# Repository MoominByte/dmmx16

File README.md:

# BenchScan DMMX16

BenchScan DMMX16 is a digital multimeter switching card inspired by the functional architecture of the SIGLENT SC1016. It provides 16 measurement channels: 12 multipurpose channels and 4 fuse-protected current channels.

## Project status

- Schematic revision: **DRAFT-1**
- File format: **KiCad 10**
- Hierarchical schematic converted and saved
- ERC: **0 errors and 18 off-grid warnings** from the custom MOSFET symbols
- PCB: **220 × 110 mm**, four copper layers, with all 113 footprints placed on the top side
- Preliminary placement completed; routing and manufacturing files have not started

This project is not ready for manufacturing.

## Opening the project

Open `BenchScan_DMMX16.kicad_pro` with KiCad 10. The modern root schematic is `BenchScan_DMMX16.kicad_sch`.

The legacy `.sch` files are retained as conversion sources. The earlier architecture-only draft is preserved under `archive/architecture-notes-draft0/`.

## Architecture

### Control

- Main module: Seeed Studio XIAO ESP32-C6, U1
- D0 / GPIO0: serial data `SER`
- D1 / GPIO1: shift clock `SRCLK`
- D2 / GPIO2: register clock `RCLK`
- D3 / GPIO21: active-low output enable `/OE`
- D4 / GPIO22: direct K17 control
- U2 and U3: two SN74HC595 shift registers powered by the XIAO 3.3 V output
- U2 controls K1-K8 and U3 controls K9-K16

Each relay is driven by a 2N7002K MOSFET with a 100 ohm series gate resistor, a 47 kohm gate pull-down, and a 1N4148W flyback diode. K17 uses the same driver circuit but receives its control signal directly from the XIAO.

### Measurement channels

| Connector | Channels | Purpose |
| --- | --- | --- |
| J1 | CH1-CH4 | Voltage, resistance, frequency, capacitance, diode, continuity, and temperature |
| J2 | CH5-CH8 | Multipurpose measurement and associated SENSE channels |
| J3 | CH9-CH12 | Multipurpose measurement and associated SENSE channels |
| J4 | CH13-CH16 | Current measurement, provisional 500 mA maximum |

Each J1-J4 connector has eight positions at 5.00 mm pitch: one `HI` and one `LO` terminal for each of its four channels.

### Switching

- K1-K16 use normally open contacts.
- K1-K6 route directly to `INPUT_HI` and `COM`.
- K7-K12 are routed through K17.
- With K17 de-energized, K7-K12 are routed to `INPUT_HI` and `COM`.
- With K17 energized, K7-K12 are routed to `SENSE_HI` and `SENSE_LO`.
- The four-wire pairs are CH1+CH7, CH2+CH8, CH3+CH9, CH4+CH10, CH5+CH11, and CH6+CH12.
- K13-K16 route the current channels to `CURRENT_HI` and `CURRENT_LO`.

Firmware must prevent multiple channels from being connected to the same destination bus at the same time, except for one valid four-wire pair.

### Current-channel protection

F1-F4 are Littelfuse `0451.500MRL` fast-acting 500 mA, 125 V fuses. They must not be replaced by 0.1 ohm resistors without a new circuit and safety analysis.

### DMM interface

J5 and the six banana jacks expose:

- `INPUT_HI`
- `COM`
- `SENSE_HI`
- `SENSE_LO`
- `CURRENT_HI`
- `CURRENT_LO`

R50 is a default-fitted 0 ohm link between `CURRENT_LO` and `COM`, with accessible test points planned on both sides.

### Power

- The XIAO is powered through its USB-C connector.
- The barrel jack supplies only the `+5V_RELAY` rail through F6 and Q19.
- USB, logic, and relay grounds are common.
- The external 5 V supply is not connected directly to the XIAO VBUS pin, preventing backfeed into USB.

## Schematic structure

- `01_power_control.kicad_sch`: XIAO, shift registers, and power supply
- `02_relay_drivers.kicad_sch`: 17 relay-coil drivers
- `03_voltage_channels.kicad_sch`: CH1-CH12 and normal/sense selection
- `04_current_dmm_interface.kicad_sch`: CH13-CH16, fuses, and DMM interface

Supporting documents:

- `BOM_AUDIT.md`: bill-of-materials review
- `CONNECTOR_PINOUT.csv`: J1-J4 pin assignments
- `SWITCHING_TRUTH_TABLE.md`: switching truth table
- `PLACEMENT_CONSTRAINTS.md`: mechanical and placement constraints
- `SC1016_REFERENCE.md`: SC1016 reference specifications
- `erc-placement.json`: latest automated ERC report
- `drc-placement.json`: preliminary placement DRC report (routing intentionally incomplete)
- `LIBRARY_SOURCES.md`: footprint provenance and manufacturer references

## Required before routing

1. Align the custom MOSFET symbol pins to eliminate the 18 ERC off-grid warnings.
2. Verify the gate, source, and drain pin mapping of Q1-Q19 against the selected SOT-23 footprint.
3. Mechanically verify the four project-created footprints against physical samples or manufacturer drawings before ordering boards.
4. Confirm voltage limits, creepage and clearance requirements, trace-width rules, and internal plane strategy.
5. Review and refine the preliminary placement, especially edge access and measurement-signal return paths.
6. Complete a manual schematic and PCB review before routing and manufacturing-output generation.

## Warning

The SC1016 ratings are used only as a functional reference. They do not certify the electrical limits of this board. A complete safety and manufacturability review is required before ordering PCBs.

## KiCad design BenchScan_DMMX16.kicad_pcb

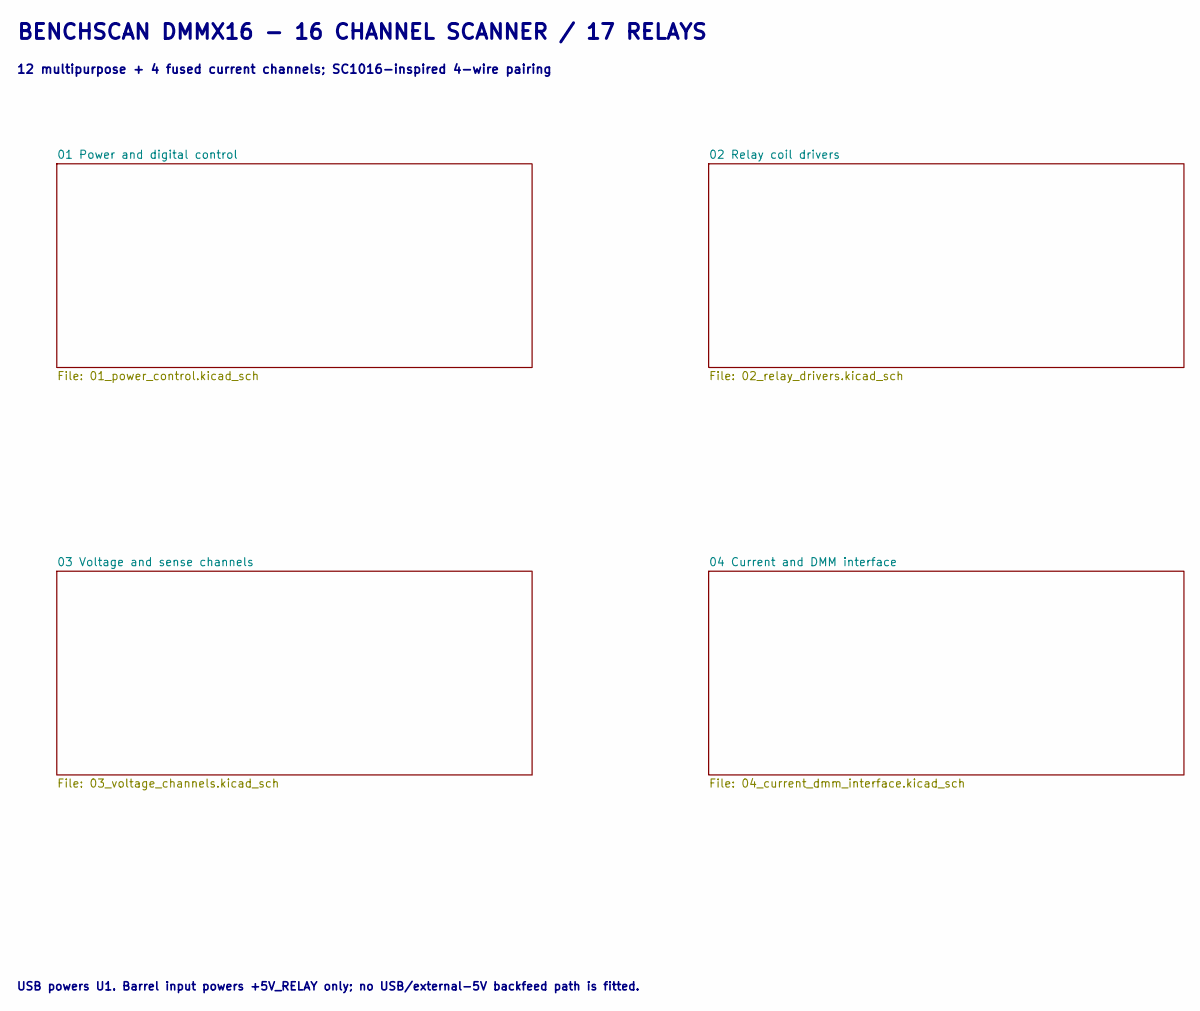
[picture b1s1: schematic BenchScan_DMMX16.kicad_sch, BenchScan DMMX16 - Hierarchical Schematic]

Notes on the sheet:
12 multipurpose + 4 fused current channels; SC1016-inspired 4-wire pairing
USB powers U1. Barrel input powers +5V_RELAY only; no USB/external-5V backfeed path is fitted.
BENCHSCAN DMMX16 - 16 CHANNEL SCANNER / 17 RELAYS

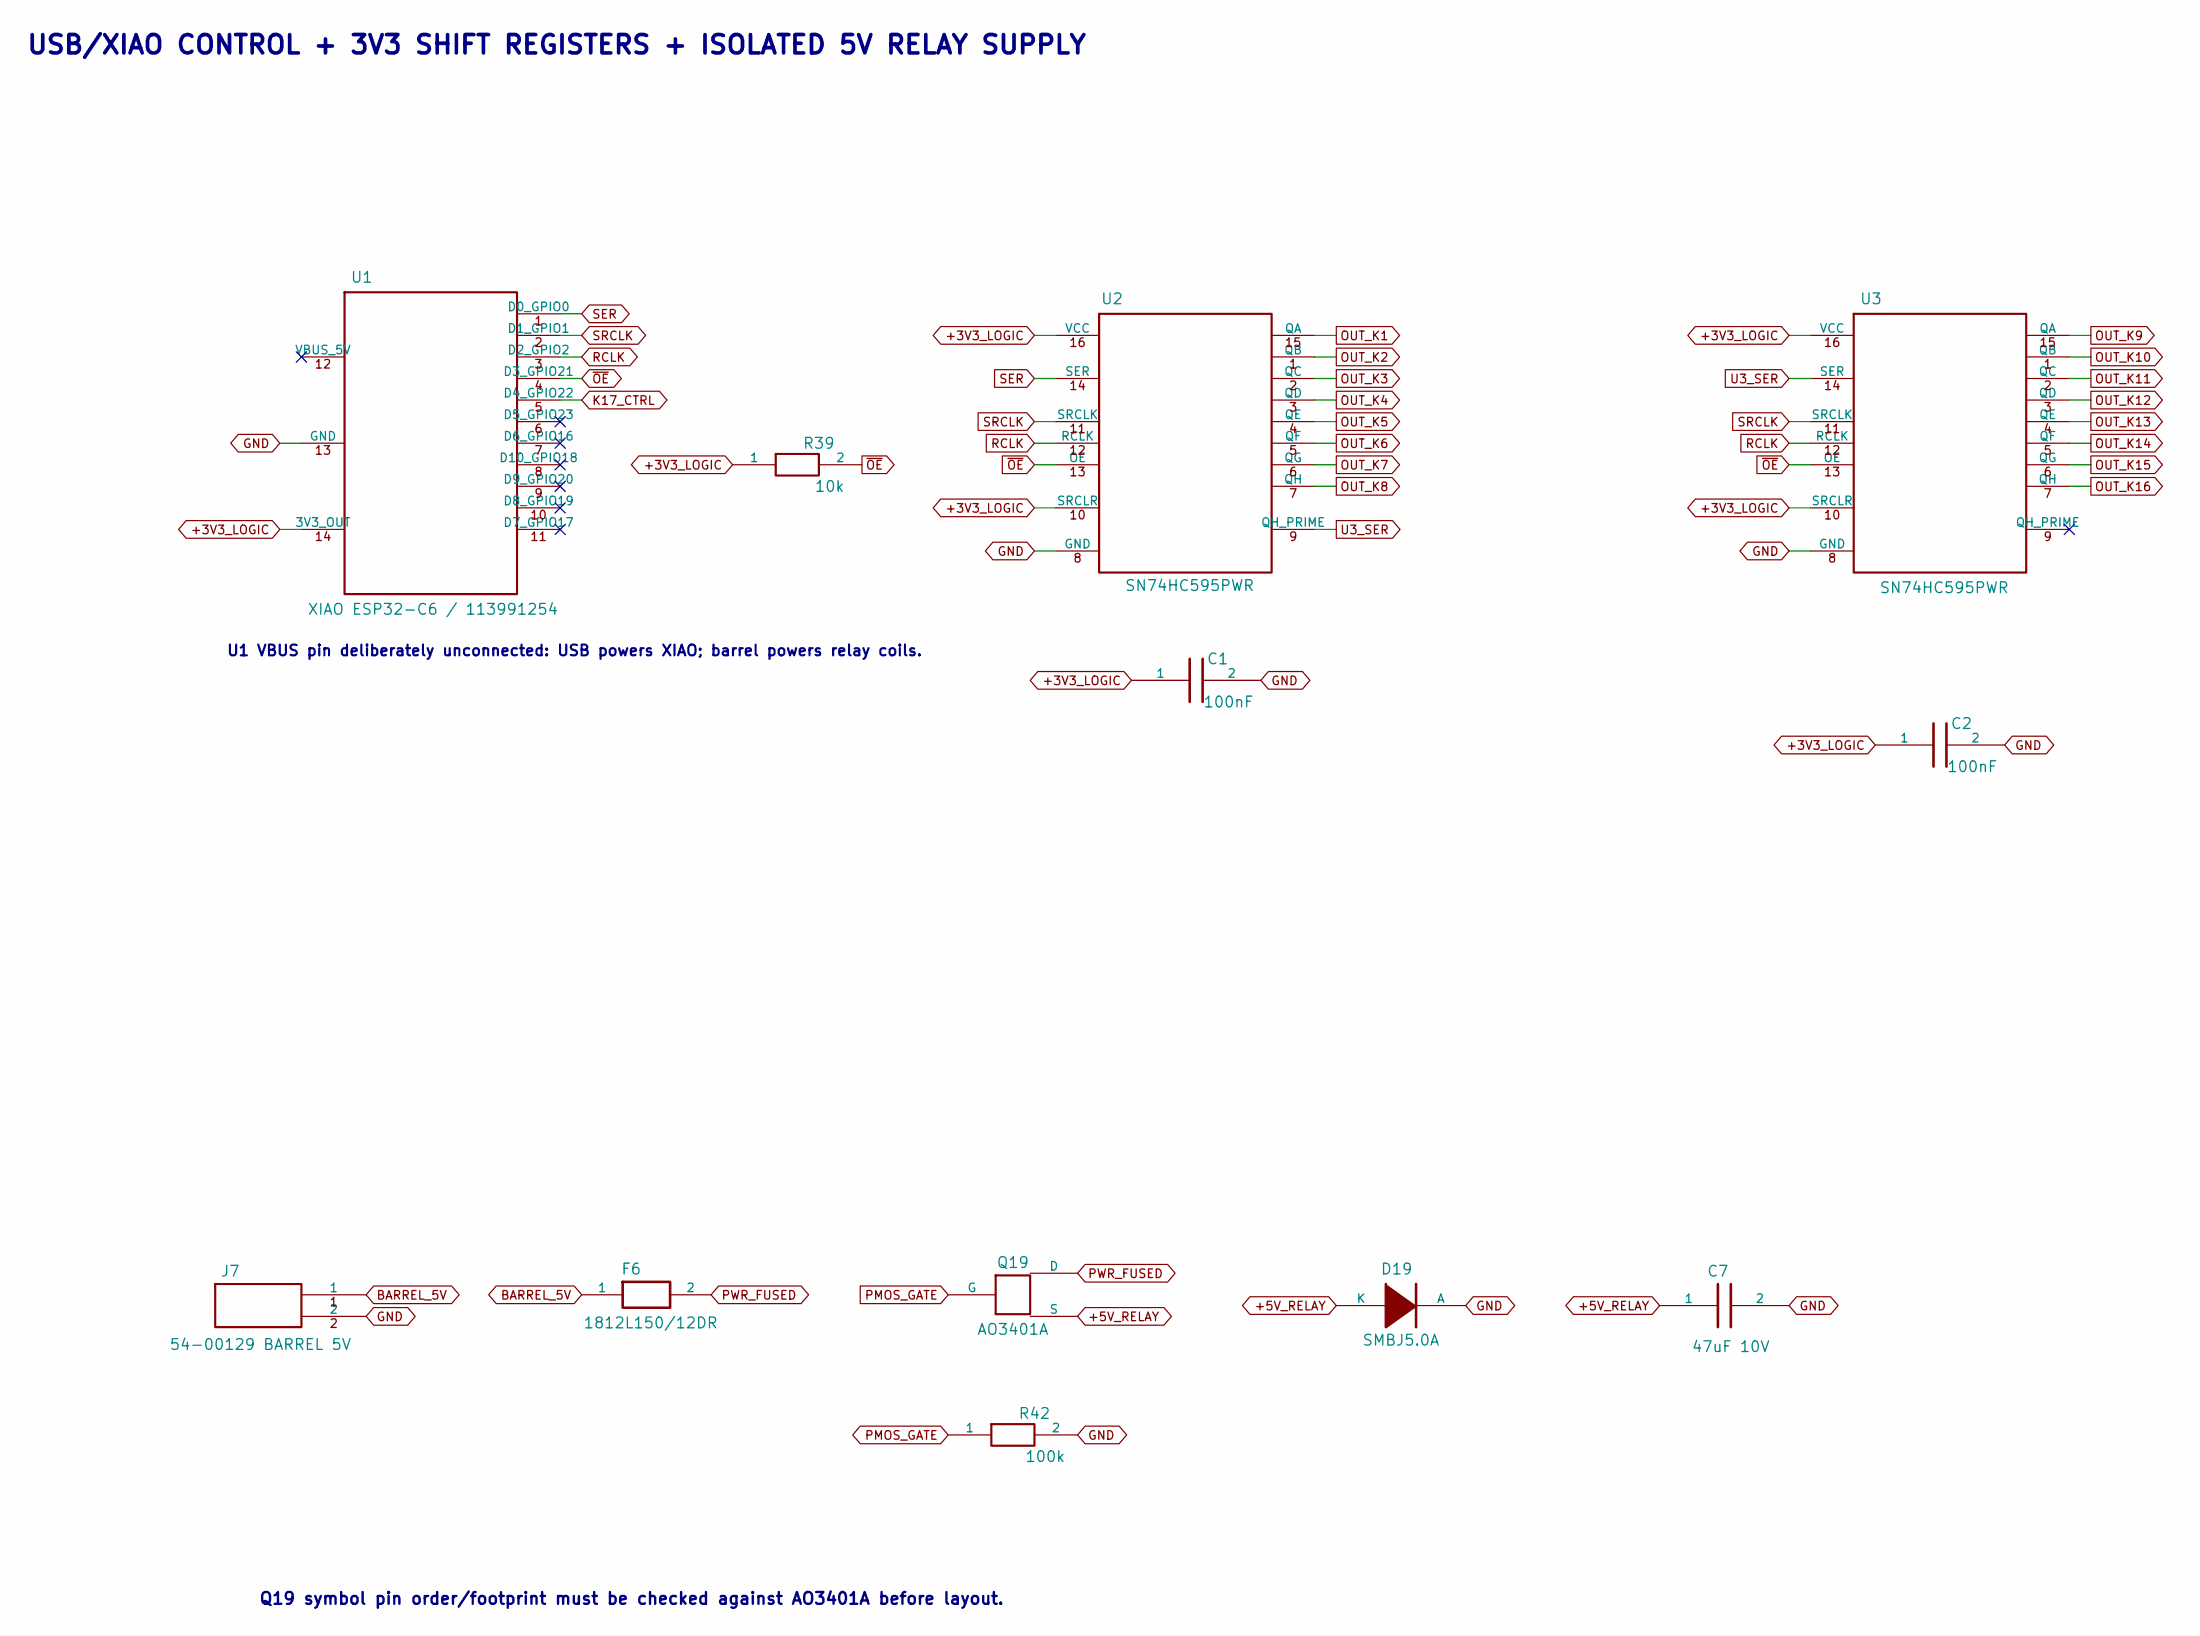
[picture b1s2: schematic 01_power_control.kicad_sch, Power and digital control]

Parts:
C1, C2: 100nF; C_0603_1608Metric
C7: 47uF 10V; C_1210_3225Metric
D19: SMBJ5.0A; D_SMB
F6: 1812L150/12DR; Fuse_1812_4532Metric
J7: 54-00129 BARREL 5V; Tensility_54-00129_DCJack
Q19: AO3401A; SOT-23
R39: 10k; R_0603_1608Metric
R42: 100k; R_0603_1608Metric
U1: XIAO ESP32-C6 / 113991254; XIAO-ESP32-C6-SMD
U2, U3: SN74HC595PWR; TSSOP-16_4.4x5mm_P0.65mm

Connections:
+3V3_LOGIC: C1.1, C2.1, R39.1, U1.14 (3V3_OUT), U2.10 (SRCLR), U2.16 (VCC), U3.10 (SRCLR), U3.16 (VCC)
+5V_RELAY: C7.1, D19.1 (K), Q19.2 (S); also elsewhere on the board
BARREL_5V: F6.1, J7.1
GND: C1.2, C2.2, C7.2, D19.2 (A), J7.2, R42.2, U1.13 (GND), U2.8 (GND), U3.8 (GND); also elsewhere on the board
K17_CTRL: U1.5 (D4_GPIO22); also elsewhere on the board
OUT_K1: U2.15 (QA); also elsewhere on the board
OUT_K2: U2.1 (QB); also elsewhere on the board
OUT_K3: U2.2 (QC); also elsewhere on the board
OUT_K4: U2.3 (QD); also elsewhere on the board
OUT_K5: U2.4 (QE); also elsewhere on the board
OUT_K6: U2.5 (QF); also elsewhere on the board
OUT_K7: U2.6 (QG); also elsewhere on the board
OUT_K8: U2.7 (QH); also elsewhere on the board
OUT_K9: U3.15 (QA); also elsewhere on the board
OUT_K10: U3.1 (QB); also elsewhere on the board
OUT_K11: U3.2 (QC); also elsewhere on the board
OUT_K12: U3.3 (QD); also elsewhere on the board
OUT_K13: U3.4 (QE); also elsewhere on the board
OUT_K14: U3.5 (QF); also elsewhere on the board
OUT_K15: U3.6 (QG); also elsewhere on the board
OUT_K16: U3.7 (QH); also elsewhere on the board
PMOS_GATE: Q19.1 (G), R42.1
PWR_FUSED: F6.2, Q19.3 (D)
RCLK: U1.3 (D2_GPIO2), U2.12 (RCLK), U3.12 (RCLK)
SER: U1.1 (D0_GPIO0), U2.14 (SER)
SRCLK: U1.2 (D1_GPIO1), U2.11 (SRCLK), U3.11 (SRCLK)
U3_SER: U2.9 (QH_PRIME), U3.14 (SER)
~OE: R39.2, U1.4 (D3_GPIO21), U2.13 (OE), U3.13 (OE)

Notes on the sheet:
USB/XIAO CONTROL + 3V3 SHIFT REGISTERS + ISOLATED 5V RELAY SUPPLY
U1 VBUS pin deliberately unconnected: USB powers XIAO; barrel powers relay coils.
Q19 symbol pin order/footprint must be checked against AO3401A before layout.

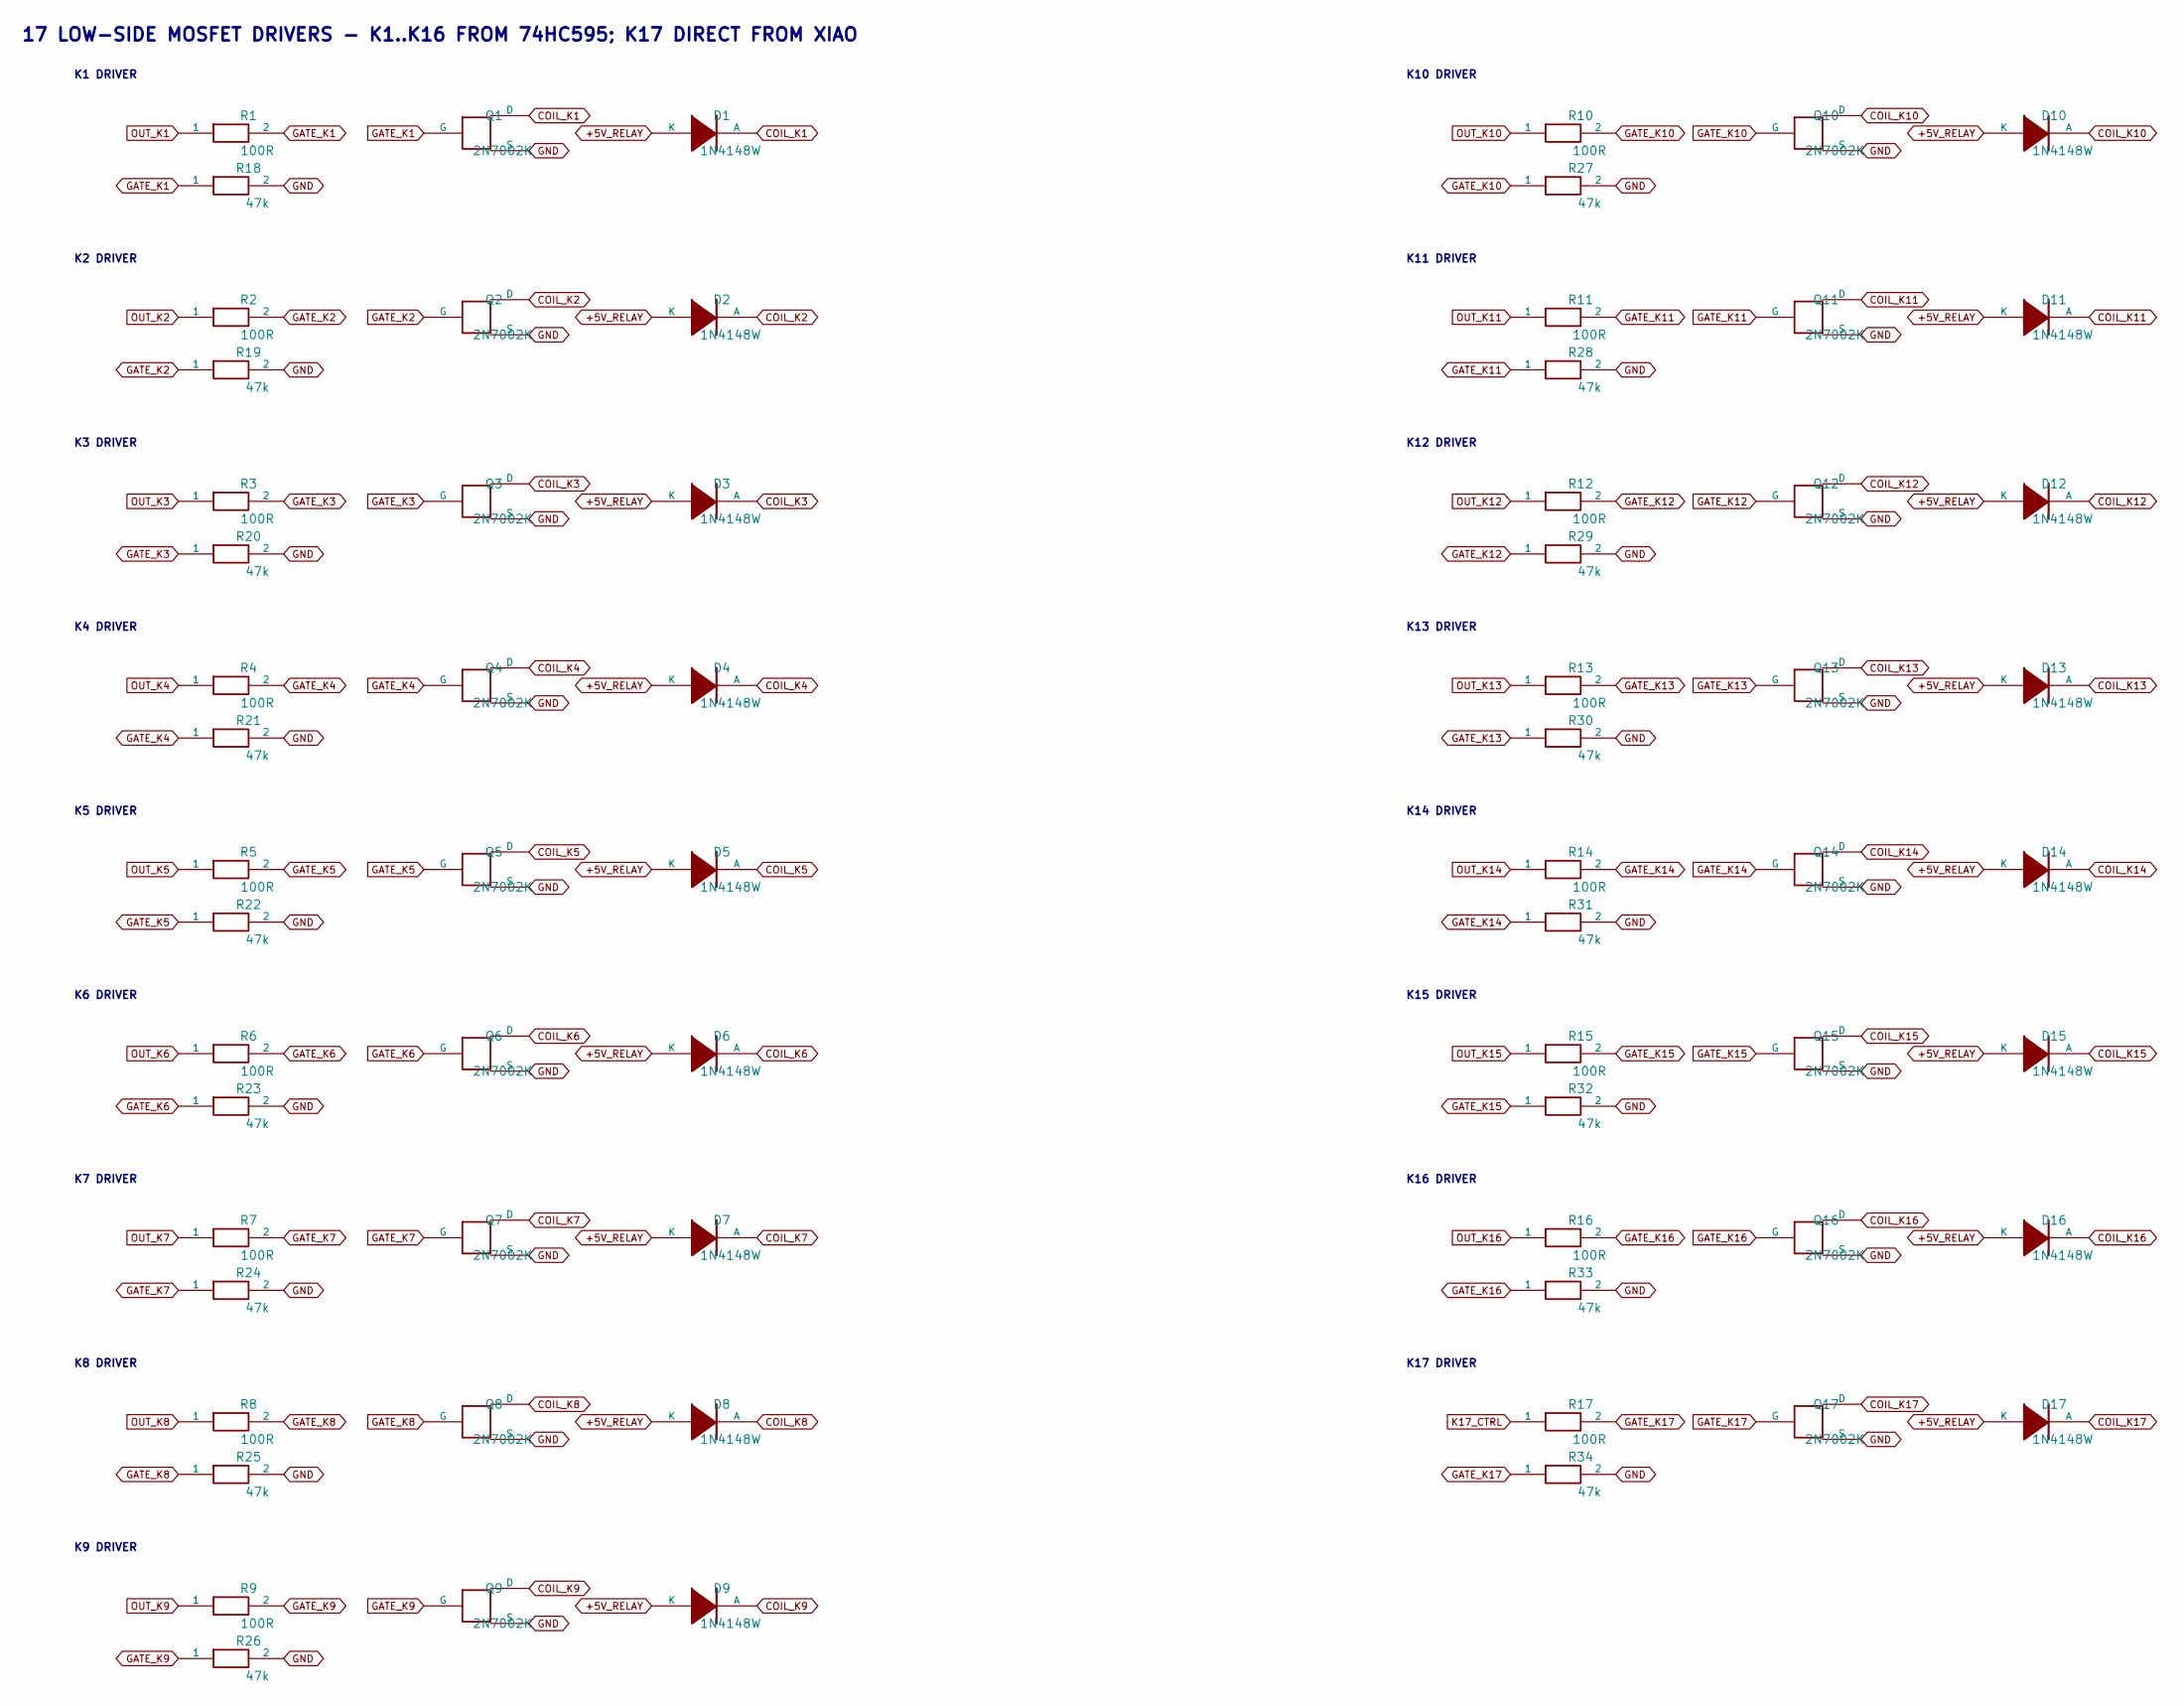
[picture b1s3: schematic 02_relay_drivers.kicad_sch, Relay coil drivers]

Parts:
D1, D2, D3, D4, D5, D6, D7, D8, D9, D10, D11, D12, D13, D14, D15, D16, D17: 1N4148W; D_SOD-123
Q1, Q2, Q3, Q4, Q5, Q6, Q7, Q8, Q9, Q10, Q11, Q12, Q13, Q14, Q15, Q16, Q17: 2N7002K; SOT-23
R1, R2, R3, R4, R5, R6, R7, R8, R9, R10, R11, R12, R13, R14, R15, R16, R17: 100R; R_0603_1608Metric
R18, R19, R20, R21, R22, R23, R24, R25, R26, R27, R28, R29, R30, R31, R32, R33, R34: 47k; R_0603_1608Metric

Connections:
+5V_RELAY: D1.1 (K), D2.1 (K), D3.1 (K), D4.1 (K), D5.1 (K), D6.1 (K), D7.1 (K), D8.1 (K), D9.1 (K), D10.1 (K), D11.1 (K), D12.1 (K), D13.1 (K), D14.1 (K), D15.1 (K), D16.1 (K), D17.1 (K); also elsewhere on the board
COIL_K1: D1.2 (A), Q1.3 (D); also elsewhere on the board
COIL_K2: D2.2 (A), Q2.3 (D); also elsewhere on the board
COIL_K3: D3.2 (A), Q3.3 (D); also elsewhere on the board
COIL_K4: D4.2 (A), Q4.3 (D); also elsewhere on the board
COIL_K5: D5.2 (A), Q5.3 (D); also elsewhere on the board
COIL_K6: D6.2 (A), Q6.3 (D); also elsewhere on the board
COIL_K7: D7.2 (A), Q7.3 (D); also elsewhere on the board
COIL_K8: D8.2 (A), Q8.3 (D); also elsewhere on the board
COIL_K9: D9.2 (A), Q9.3 (D); also elsewhere on the board
COIL_K10: D10.2 (A), Q10.3 (D); also elsewhere on the board
COIL_K11: D11.2 (A), Q11.3 (D); also elsewhere on the board
COIL_K12: D12.2 (A), Q12.3 (D); also elsewhere on the board
COIL_K13: D13.2 (A), Q13.3 (D); also elsewhere on the board
COIL_K14: D14.2 (A), Q14.3 (D); also elsewhere on the board
COIL_K15: D15.2 (A), Q15.3 (D); also elsewhere on the board
COIL_K16: D16.2 (A), Q16.3 (D); also elsewhere on the board
COIL_K17: D17.2 (A), Q17.3 (D); also elsewhere on the board
GATE_K1: Q1.1 (G), R1.2, R18.1
GATE_K2: Q2.1 (G), R2.2, R19.1
GATE_K3: Q3.1 (G), R3.2, R20.1
GATE_K4: Q4.1 (G), R4.2, R21.1
GATE_K5: Q5.1 (G), R5.2, R22.1
GATE_K6: Q6.1 (G), R6.2, R23.1
GATE_K7: Q7.1 (G), R7.2, R24.1
GATE_K8: Q8.1 (G), R8.2, R25.1
GATE_K9: Q9.1 (G), R9.2, R26.1
GATE_K10: Q10.1 (G), R10.2, R27.1
GATE_K11: Q11.1 (G), R11.2, R28.1
GATE_K12: Q12.1 (G), R12.2, R29.1
GATE_K13: Q13.1 (G), R13.2, R30.1
GATE_K14: Q14.1 (G), R14.2, R31.1
GATE_K15: Q15.1 (G), R15.2, R32.1
GATE_K16: Q16.1 (G), R16.2, R33.1
GATE_K17: Q17.1 (G), R17.2, R34.1
GND: Q1.2 (S), Q2.2 (S), Q3.2 (S), Q4.2 (S), Q5.2 (S), Q6.2 (S), Q7.2 (S), Q8.2 (S), Q9.2 (S), Q10.2 (S), Q11.2 (S), Q12.2 (S), Q13.2 (S), Q14.2 (S), Q15.2 (S), Q16.2 (S), Q17.2 (S), R18.2, R19.2, R20.2, R21.2, R22.2, R23.2, R24.2, R25.2, R26.2, R27.2, R28.2, R29.2, R30.2, R31.2, R32.2, R33.2, R34.2; also elsewhere on the board
K17_CTRL: R17.1; also elsewhere on the board
OUT_K1: R1.1; also elsewhere on the board
OUT_K2: R2.1; also elsewhere on the board
OUT_K3: R3.1; also elsewhere on the board
OUT_K4: R4.1; also elsewhere on the board
OUT_K5: R5.1; also elsewhere on the board
OUT_K6: R6.1; also elsewhere on the board
OUT_K7: R7.1; also elsewhere on the board
OUT_K8: R8.1; also elsewhere on the board
OUT_K9: R9.1; also elsewhere on the board
OUT_K10: R10.1; also elsewhere on the board
OUT_K11: R11.1; also elsewhere on the board
OUT_K12: R12.1; also elsewhere on the board
OUT_K13: R13.1; also elsewhere on the board
OUT_K14: R14.1; also elsewhere on the board
OUT_K15: R15.1; also elsewhere on the board
OUT_K16: R16.1; also elsewhere on the board

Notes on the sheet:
K17 DRIVER
K9 DRIVER
K10 DRIVER
K2 DRIVER
K15 DRIVER
K3 DRIVER
K12 DRIVER
K6 DRIVER
K13 DRIVER
K7 DRIVER
K14 DRIVER
K8 DRIVER
K5 DRIVER
K4 DRIVER
K11 DRIVER
K1 DRIVER
17 LOW-SIDE MOSFET DRIVERS - K1..K16 FROM 74HC595; K17 DIRECT FROM XIAO
K16 DRIVER

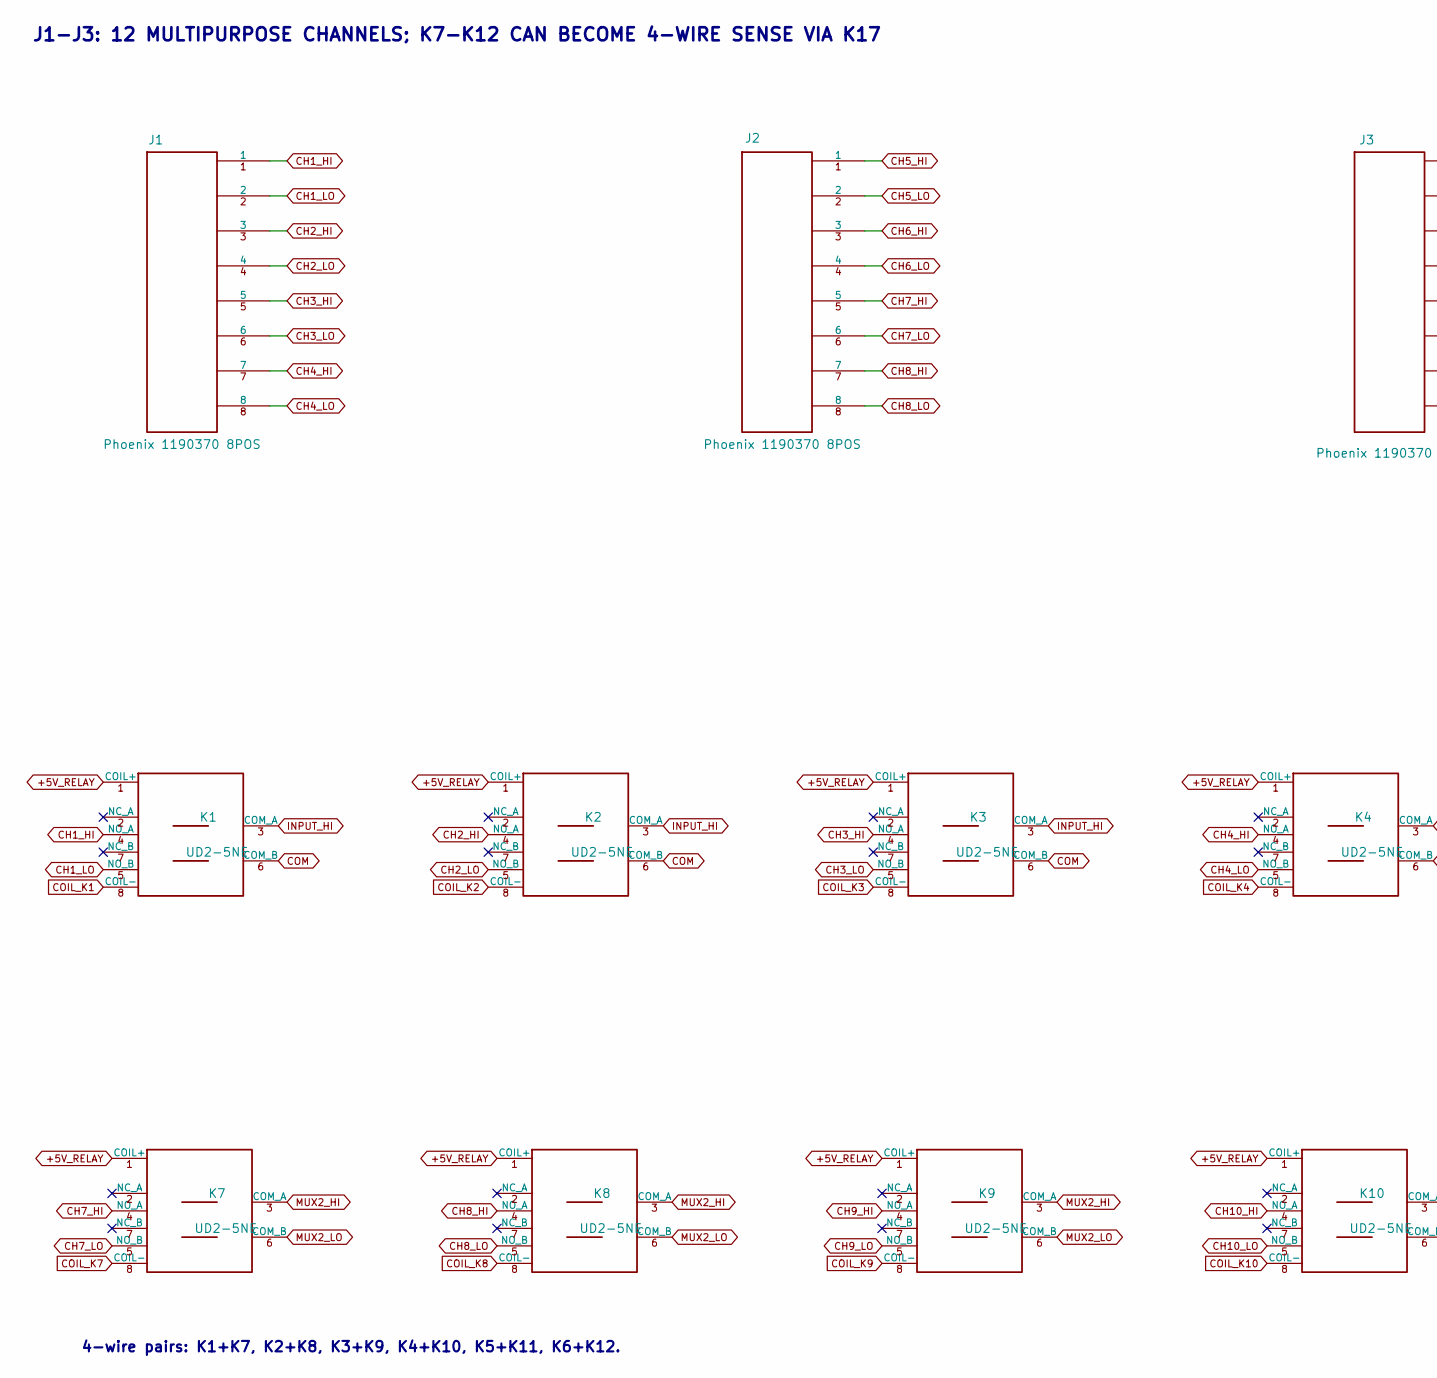
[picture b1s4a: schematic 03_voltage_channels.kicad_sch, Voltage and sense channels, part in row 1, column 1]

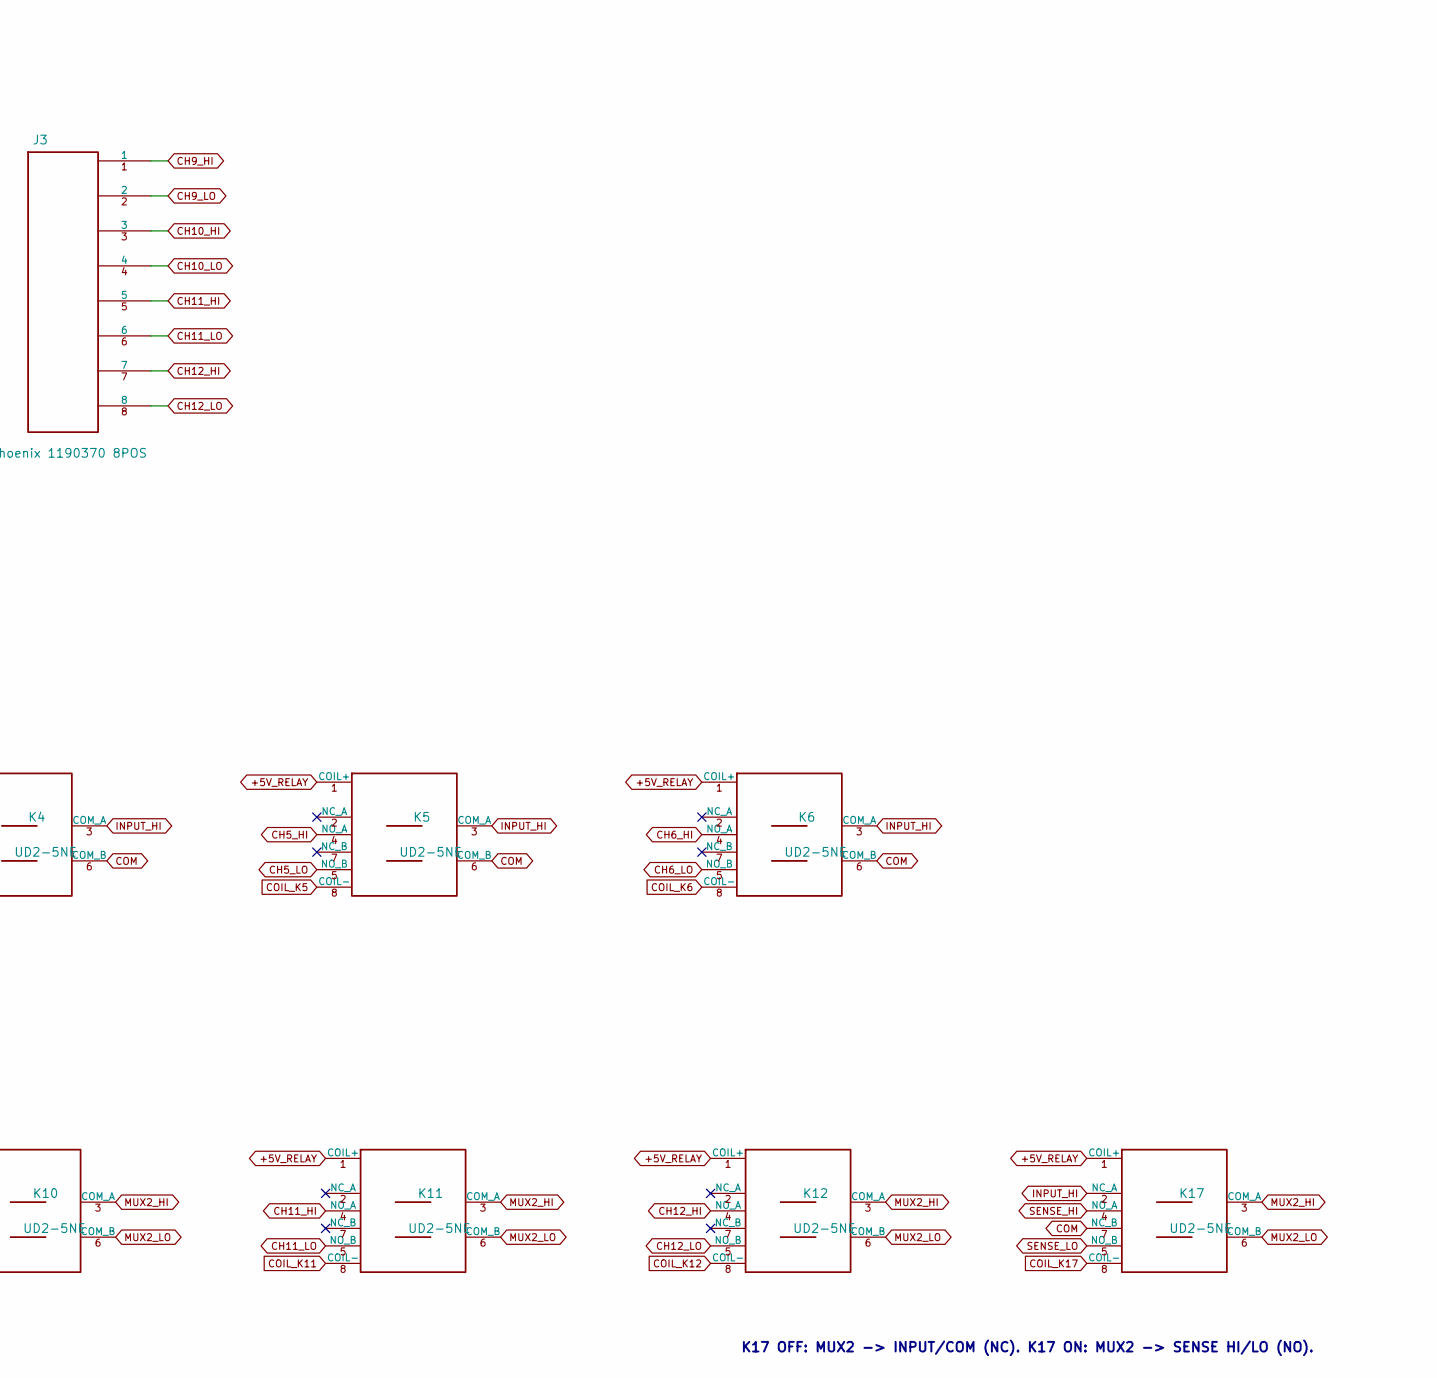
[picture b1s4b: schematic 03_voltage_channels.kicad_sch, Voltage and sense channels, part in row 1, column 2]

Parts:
J1, J2, J3: Phoenix 1190370 8POS; Phoenix_1190370_LPTA-2.5-8-5.0_16THT_Paired
K1, K2, K3, K4, K5, K6, K7, K8, K9, K10, K11, K12, K17: UD2-5NE; Relay_KEMET_UD2_NE

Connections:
+5V_RELAY: K1.1 (COIL+), K2.1 (COIL+), K3.1 (COIL+), K4.1 (COIL+), K5.1 (COIL+), K6.1 (COIL+), K7.1 (COIL+), K8.1 (COIL+), K9.1 (COIL+), K10.1 (COIL+), K11.1 (COIL+), K12.1 (COIL+), K17.1 (COIL+); also elsewhere on the board
CH1_HI: J1.1, K1.4 (NO_A)
CH1_LO: J1.2, K1.5 (NO_B)
CH2_HI: J1.3, K2.4 (NO_A)
CH2_LO: J1.4, K2.5 (NO_B)
CH3_HI: J1.5, K3.4 (NO_A)
CH3_LO: J1.6, K3.5 (NO_B)
CH4_HI: J1.7, K4.4 (NO_A)
CH4_LO: J1.8, K4.5 (NO_B)
CH5_HI: J2.1, K5.4 (NO_A)
CH5_LO: J2.2, K5.5 (NO_B)
CH6_HI: J2.3, K6.4 (NO_A)
CH6_LO: J2.4, K6.5 (NO_B)
CH7_HI: J2.5, K7.4 (NO_A)
CH7_LO: J2.6, K7.5 (NO_B)
CH8_HI: J2.7, K8.4 (NO_A)
CH8_LO: J2.8, K8.5 (NO_B)
CH9_HI: J3.1, K9.4 (NO_A)
CH9_LO: J3.2, K9.5 (NO_B)
CH10_HI: J3.3, K10.4 (NO_A)
CH10_LO: J3.4, K10.5 (NO_B)
CH11_HI: J3.5, K11.4 (NO_A)
CH11_LO: J3.6, K11.5 (NO_B)
CH12_HI: J3.7, K12.4 (NO_A)
CH12_LO: J3.8, K12.5 (NO_B)
COIL_K1: K1.8 (COIL-); also elsewhere on the board
COIL_K2: K2.8 (COIL-); also elsewhere on the board
COIL_K3: K3.8 (COIL-); also elsewhere on the board
COIL_K4: K4.8 (COIL-); also elsewhere on the board
COIL_K5: K5.8 (COIL-); also elsewhere on the board
COIL_K6: K6.8 (COIL-); also elsewhere on the board
COIL_K7: K7.8 (COIL-); also elsewhere on the board
COIL_K8: K8.8 (COIL-); also elsewhere on the board
COIL_K9: K9.8 (COIL-); also elsewhere on the board
COIL_K10: K10.8 (COIL-); also elsewhere on the board
COIL_K11: K11.8 (COIL-); also elsewhere on the board
COIL_K12: K12.8 (COIL-); also elsewhere on the board
COIL_K17: K17.8 (COIL-); also elsewhere on the board
COM: K1.6 (COM_B), K2.6 (COM_B), K3.6 (COM_B), K4.6 (COM_B), K5.6 (COM_B), K6.6 (COM_B), K17.7 (NC_B); also elsewhere on the board
INPUT_HI: K1.3 (COM_A), K2.3 (COM_A), K3.3 (COM_A), K4.3 (COM_A), K5.3 (COM_A), K6.3 (COM_A), K17.2 (NC_A); also elsewhere on the board
MUX2_HI: K7.3 (COM_A), K8.3 (COM_A), K9.3 (COM_A), K10.3 (COM_A), K11.3 (COM_A), K12.3 (COM_A), K17.3 (COM_A)
MUX2_LO: K7.6 (COM_B), K8.6 (COM_B), K9.6 (COM_B), K10.6 (COM_B), K11.6 (COM_B), K12.6 (COM_B), K17.6 (COM_B)
SENSE_HI: K17.4 (NO_A); also elsewhere on the board
SENSE_LO: K17.5 (NO_B); also elsewhere on the board

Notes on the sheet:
4-wire pairs: K1+K7, K2+K8, K3+K9, K4+K10, K5+K11, K6+K12.
K17 OFF: MUX2 -> INPUT/COM (NC). K17 ON: MUX2 -> SENSE HI/LO (NO).
J1-J3: 12 MULTIPURPOSE CHANNELS; K7-K12 CAN BECOME 4-WIRE SENSE VIA K17
